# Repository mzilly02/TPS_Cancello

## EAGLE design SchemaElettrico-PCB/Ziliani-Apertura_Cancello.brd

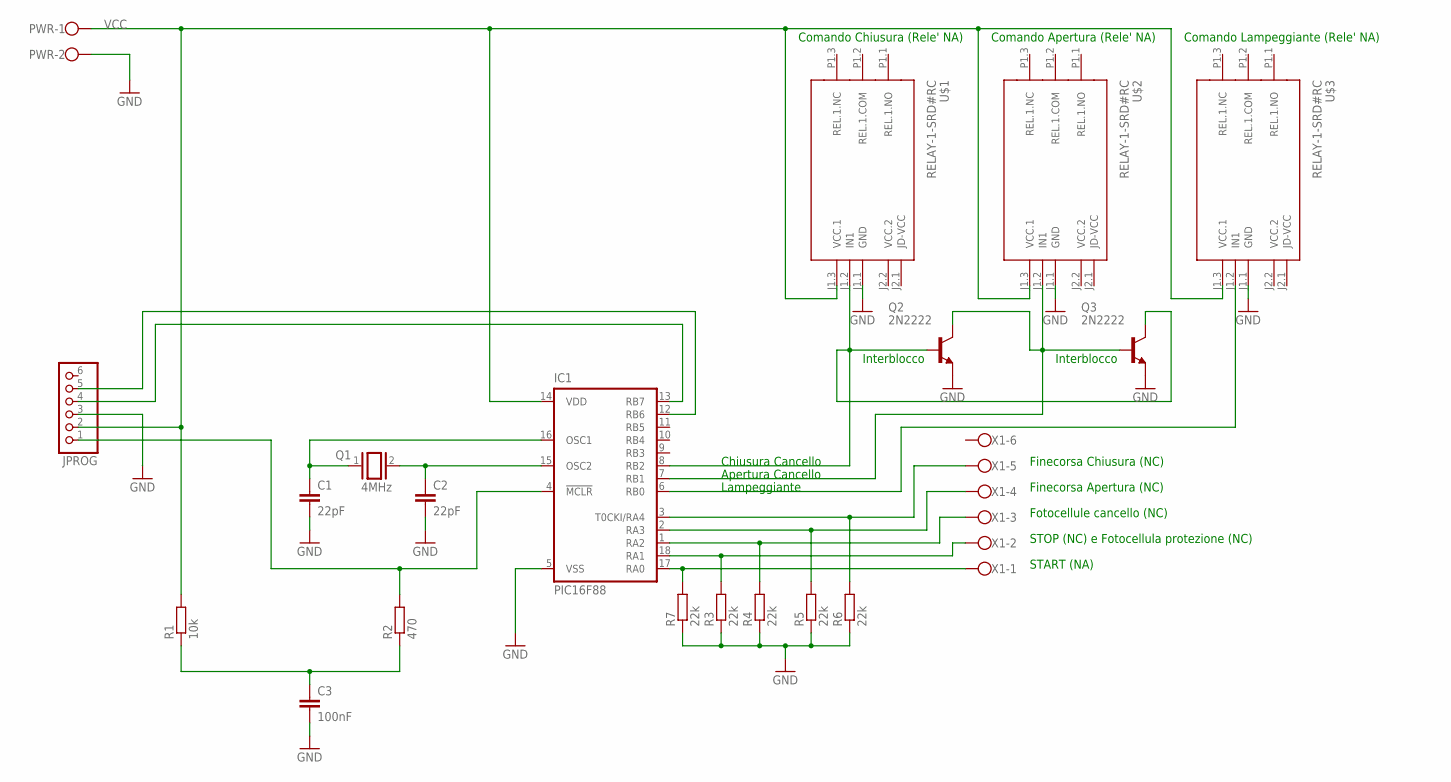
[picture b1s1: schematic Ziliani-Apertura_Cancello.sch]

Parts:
C1, C2: 22pF; C025-025X050
C3: 100nF; C025-025X050
IC1: PIC16F88; DIL18
JPROG: PINHD-1X6/90; 1X06/90
PWR: W237-102
Q1: 4MHz; QS
Q2, Q3: 2N2222; TO18
R1: 10k; 0207/10
R2: 470; 0207/10
R3, R4, R5, R6, R7: 22k; 0207/10
U$1, U$2, U$3: RELAY-1-SRD#RC
X1: W237-6

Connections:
GND: C1.2, C2.2, C3.2, IC1.5 (VSS), JPROG.3, PWR.2, Q2.1 (E), Q3.1 (E), R3.1, R4.1, R5.1, R6.1, R7.1, U$1.J1.1 (GND), U$2.J1.1 (GND), U$3.J1.1 (GND)
unnamed: C1.1, IC1.16 (OSC1), Q1.1
unnamed: C2.1, IC1.15 (OSC2), Q1.2
unnamed: IC1.17 (RA0), R7.2, X1.1
unnamed: IC1.4 (!MCLR), JPROG.1, R2.2
unnamed: IC1.7 (RB1), Q2.3 (C), Q3.2 (B), U$2.J1.2 (IN1)
unnamed: IC1.13 (RB7), JPROG.4
unnamed: IC1.12 (RB6), JPROG.5
unnamed: IC1.18 (RA1), R3.2, X1.2
unnamed: IC1.1 (RA2), R4.2, X1.3
unnamed: IC1.2 (RA3), R5.2, X1.4
unnamed: IC1.3 (T0CKI/RA4), R6.2, X1.5
unnamed: IC1.8 (RB2), Q2.2 (B), Q3.3 (C), U$1.J1.2 (IN1)
unnamed: C3.1, R1.1, R2.1
unnamed: IC1.6 (RB0), U$3.J1.2 (IN1)
VCC: IC1.14 (VDD), JPROG.2, PWR.1, R1.2, U$1.J1.3 (VCC.1), U$2.J1.3 (VCC.1), U$3.J1.3 (VCC.1)
VCC.2: U$1.J2.2 (VCC.2), U$2.J2.2 (VCC.2), U$3.J2.2 (VCC.2)

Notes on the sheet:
Fotocellule cancello (NC)
START (NA)
STOP (NC) e Fotocellula protezione (NC)
Finecorsa Apertura (NC)
Finecorsa Chiusura (NC)
Comando Apertura (Rele' NA)
Comando Chiusura (Rele' NA)
Lampeggiante
Comando Lampeggiante (Rele' NA)
Apertura Cancello
Chiusura Cancello
Interblocco

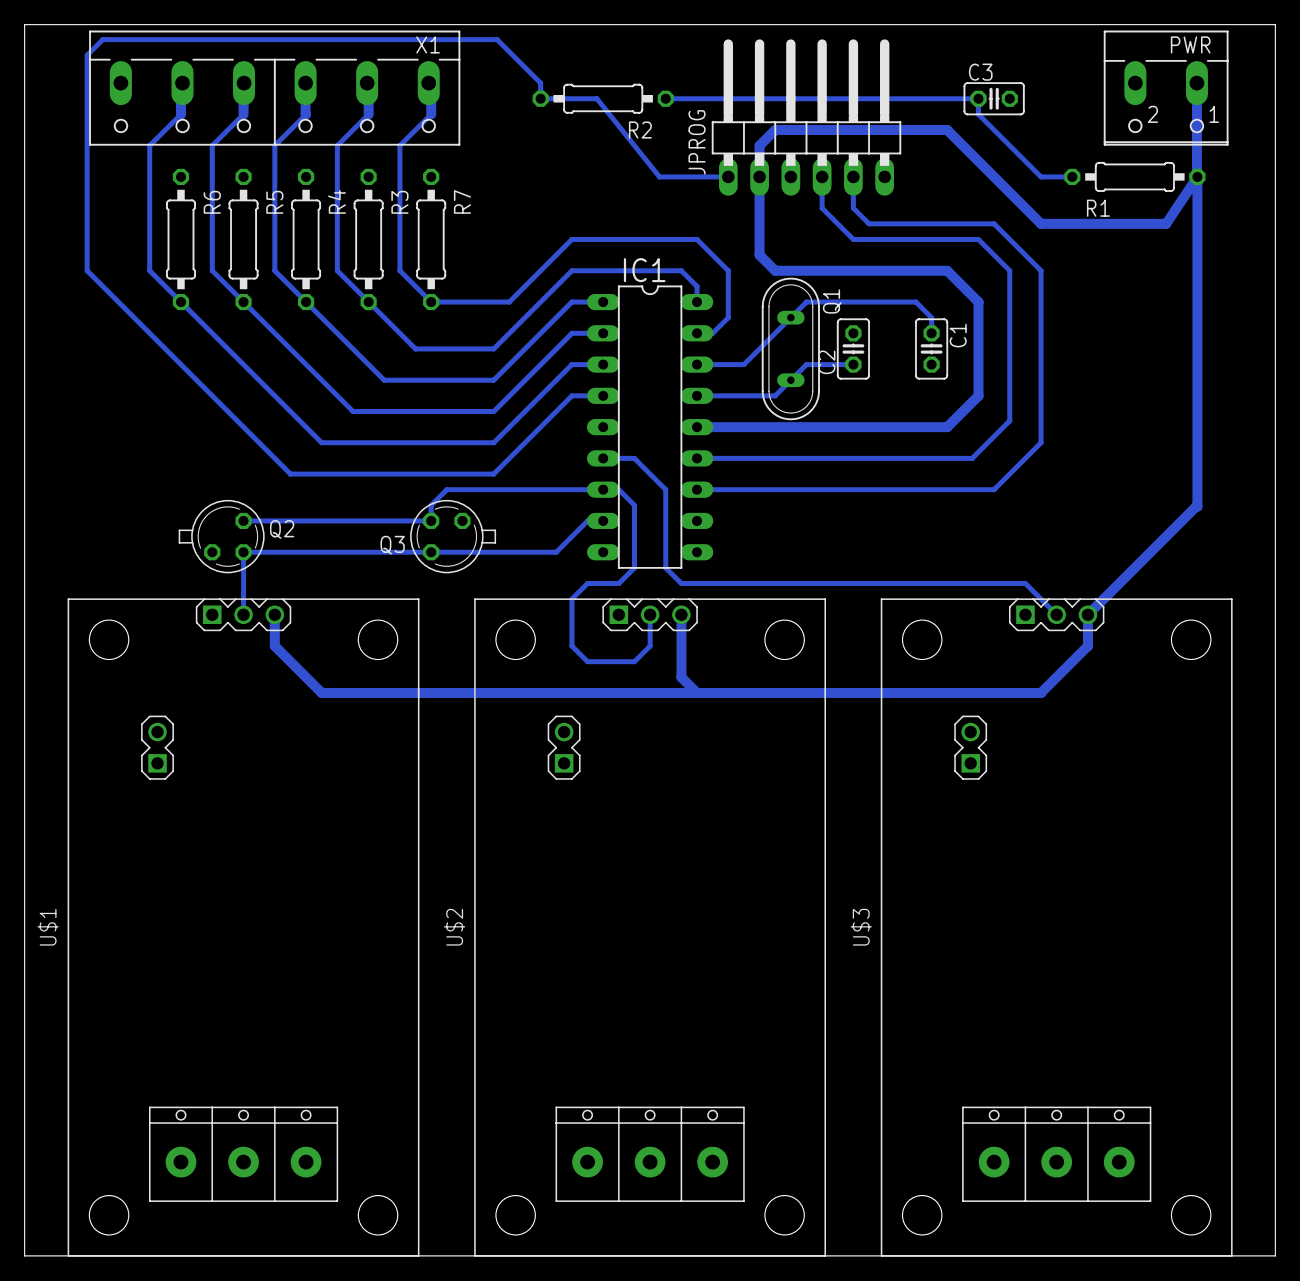
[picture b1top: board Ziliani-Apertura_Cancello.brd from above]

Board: 2 copper layers, 101.6 x 100.0 mm, 20 parts (0 on the bottom side), 17 nets.

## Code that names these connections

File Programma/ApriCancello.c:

// ApriCancello_B - Mattia Ziliani

#include <pic.h>

// Configuration bit
__CONFIG(0x3F61);

// Input
#define	P_START						RA0		// Pulsante "START" (NA)
#define	P_STOP_F_AZIONAMENTO		RA1		// Pulsante "STOP" e Fotocellula zona azionamento (entrambi NC)
#define	F_CELLULA_CANCELLO			RA2		// Fotocellula zona cancello (NC)
#define	FNC_APERTURA				RA3		// Finecorsa apertura (NC)
#define	FNC_CHIUSURA				RA4		// Finecorsa chiusura (NC)

// Output
#define	LMP_SEGNALAZIONE			RB0		// Controllo Lampeggiante (NA)
#define	CMD_APERTURA				RB1		// Controllo motore AC per apertura (NA - CW - Senso orario)
#define	CMD_CHIUSURA				RB2		// Controllo motore AC per chiusura (NA - CCW - Senso Antiorario)


// Contatori per timer
unsigned int LMP_TMR0;						// Contatore per tempo Lampeggiante
unsigned int ACT_TMR0;						// Contatore per tempo azioni

// Definizione tempi
#define TEMPO_30_SEC	600
#define TEMPO_10_SEC	200
#define TEMPO_2_SEC		40
#define TEMPO_1_SEC		20 

// Variabile di Stato
unsigned char STATO = 0;

void main(void)
{
	// Inizializzazione
	// Tutti gli ingressi digitali
	ANSEL = 0;
	OPTION_REG = 0;

	// 0 = OUTPUT ; 1 = INPUT
	TRISA = 0b00011111;	// 4 input in banco GPIO A
	PORTA = 0;
	TRISB = 0b00000000;	// 3 output in banco GPIO B
	PORTB = 0;

	// Abilita Timer0
	// ---------------
	// Fosc = 4 MHz
	// Fosc/4 = 1,0 MHz
	// Prescaler = :256 
	// F clock ((fosc/4)/Prescaler)= 3906,25 kHz
	// T = 1/ f clock = 256 _us
	// Periodo = T * 256 = 65,536 ms (intervallo 0 / 256)

	T0CS = 0;	// clock interno Fosc/4
	PSA = 0;	// Prescaler assegnato al Timer 0
	// Prescaler :256
	PS0 = 1;	
	PS1 = 1;
	PS2 = 1;
	// Precarica Timer0 in modo da generare interrupt ogni 50 ms (intervallo 60 / 256)
	// Periodo = T * 196 = 50,176 ms
	TMR0 = 60;

	// Attiva interrupt Timer 0
	TMR0IE = 1;
	// Attiva interrupt globali
	GIE = 1;

	STATO = 0; //Inizio dallo stato 0, Cancello chiuso
	
	//loop
	while (1)
	{
		//Transizione stati
		switch(STATO)
		{
			case 0:	// Cancello Chiuso
				//Vengono impostati a 0 i due rele' di comando del motore
				CMD_APERTURA = 0;
				CMD_CHIUSURA = 0;

				//Apri il cancello
				if (P_START == 1)
				{
					STATO = 1;				//Passa a stato Apertura cancello
				}
				break;

			case 1:	// Apertura cancello
				//Commutazione Lampeggiante segnalazione
				if(LMP_SEGNALAZIONE == 0)
				{
					//Accende Lampeggiante segnalazione
					LMP_SEGNALAZIONE = 1;
					LMP_TMR0 = TEMPO_1_SEC; //Tempo LMP acceso
				}
				else
				{
					//Spegne Lampeggiante segnalazione
					LMP_SEGNALAZIONE = 0;
					LMP_TMR0 = TEMPO_1_SEC; //Tempo LMP spento
				}

				//Attiva movimento CW motore AC (apertura cancello)
				CMD_APERTURA = 1;		
				CMD_CHIUSURA = 0;
				
				//blocco cancello per passaggio temporaneo
				if (P_START == 1)
				{
					STATO = 4;				//Passa a fermo temporaneo cancello
				}

				//Stop movimento
				if (P_STOP_F_AZIONAMENTO == 0)
				{
					STATO = 5;				//Blocco sistema
				}

				//Finecorsa cancello aperto attivato
				if (FNC_APERTURA == 0)
				{
					//Viene fermato l'azionamento del motore AC
					CMD_APERTURA = 0;
					CMD_CHIUSURA = 0;

					LMP_SEGNALAZIONE = 0;	//Spegni Lampeggiante segnalazione
					STATO = 2;				//Passa a stato Aperto
				}
				break;

			case 2:	// Cancello aperto
				//Chiudi il cancello
				if (P_START == 1)
				{
					STATO = 3;				//Passa a stato Chiusura cancello
				}

				//Chiusura automatica cancello
				if (ACT_TMR0 == 0)
				{	
					ACT_TMR0 = TEMPO_30_SEC;// Tempo Chiusura automatica
					STATO = 3;
				}
				break;

			case 3:	// Chiusura cancello
				//Commutazione Lampeggiante segnalazione
				if(LMP_SEGNALAZIONE == 0)
				{
					//Accende Lampeggiante segnalazione
					LMP_SEGNALAZIONE = 1;
					LMP_TMR0 = TEMPO_1_SEC; //Tempo LMP acceso
				}
				else
				{
					//Spegne Lampeggiante segnalazione
					LMP_SEGNALAZIONE = 0;
					LMP_TMR0 = TEMPO_1_SEC; //Tempo LMP spento
				}

				//Attiva movimento CCW motore AC (chiusura cancello)
				CMD_APERTURA = 0;		
				CMD_CHIUSURA = 1;
				
				//Ri-apertura cancello
				if (P_START == 1 || F_CELLULA_CANCELLO == 0)
				{
					//Viene fermato l'azionamento del motore AC
					CMD_APERTURA = 0;
					CMD_CHIUSURA = 0;

					//Inverti movimento
					if (ACT_TMR0 == 0)
					{	
						ACT_TMR0 = TEMPO_2_SEC;	//Tempo Inversione
						STATO = 1;				//Passa a stato Apertura cancello
					}
				}

				//Stop movimento
				if (P_STOP_F_AZIONAMENTO == 0)
				{
					STATO = 5;					//Blocco sistema
				}		
		
				//Finecorsa cancello chiuso attivato
				if (FNC_CHIUSURA == 0)
				{
					//Viene fermato l'azionamento del motore AC
					CMD_APERTURA = 0;
					CMD_CHIUSURA = 0;

					LMP_SEGNALAZIONE = 0;	//Spegni Lampeggiante segnalazione
					STATO = 0;				//Passa a stato Chiuso
				}
				break;

			case 4:	// Fermo temporaneo
				//Viene fermato l'azionamento del motore AC
				CMD_APERTURA = 0;
				CMD_CHIUSURA = 0;
				
				//Aspetta
				if (ACT_TMR0 == 0)
				{	
					ACT_TMR0 = TEMPO_10_SEC;	//Tempo Passaggio temporaneo
					STATO = 1;					//Passa a stato Apertura cancello
				}
				break;

			case 5: // STOP
				//Viene fermato l'azionamento del motore AC
				CMD_APERTURA = 0;
				CMD_CHIUSURA = 0;

				//Accende Lampeggiante segnalazione
				LMP_SEGNALAZIONE = 1;
				
				//Ri-apertura cancello
				if (P_START == 1)
				{
					STATO = 1;					//Passa a stato Apertura cancello
				}
				break;
			
			default:
				STATO = 0;
				break;
		}
		
	}
}

//funzione per uso interrupt
void interrupt irq()
{
	// Timer 0
	if (TMR0IF == 1)
	{
		// Flag Interrupt Timer0
		TMR0IF = 0;

		// Precarica Timer 0 in modo da generare interrupt ogni 50 ms (intervallo 60 / 256)
		// Periodo = T * 196 = 50,176 ms
		TMR0 = 60;

		// Decremento variabile contatori
		if (LMP_TMR0 > 0)
			LMP_TMR0--;
		
		if (ACT_TMR0 > 0)
			ACT_TMR0--;

	}
}

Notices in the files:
parts and their libraries:
diy-modules-PCB: Released under the Creative Commons Attribution 4.0 International License: http://creativecommons.org/licenses/by/4.0
